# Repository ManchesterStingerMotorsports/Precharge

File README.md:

# Precharge
Circuit used to prepare the vehicle side of the TS for the full accumulator voltage.

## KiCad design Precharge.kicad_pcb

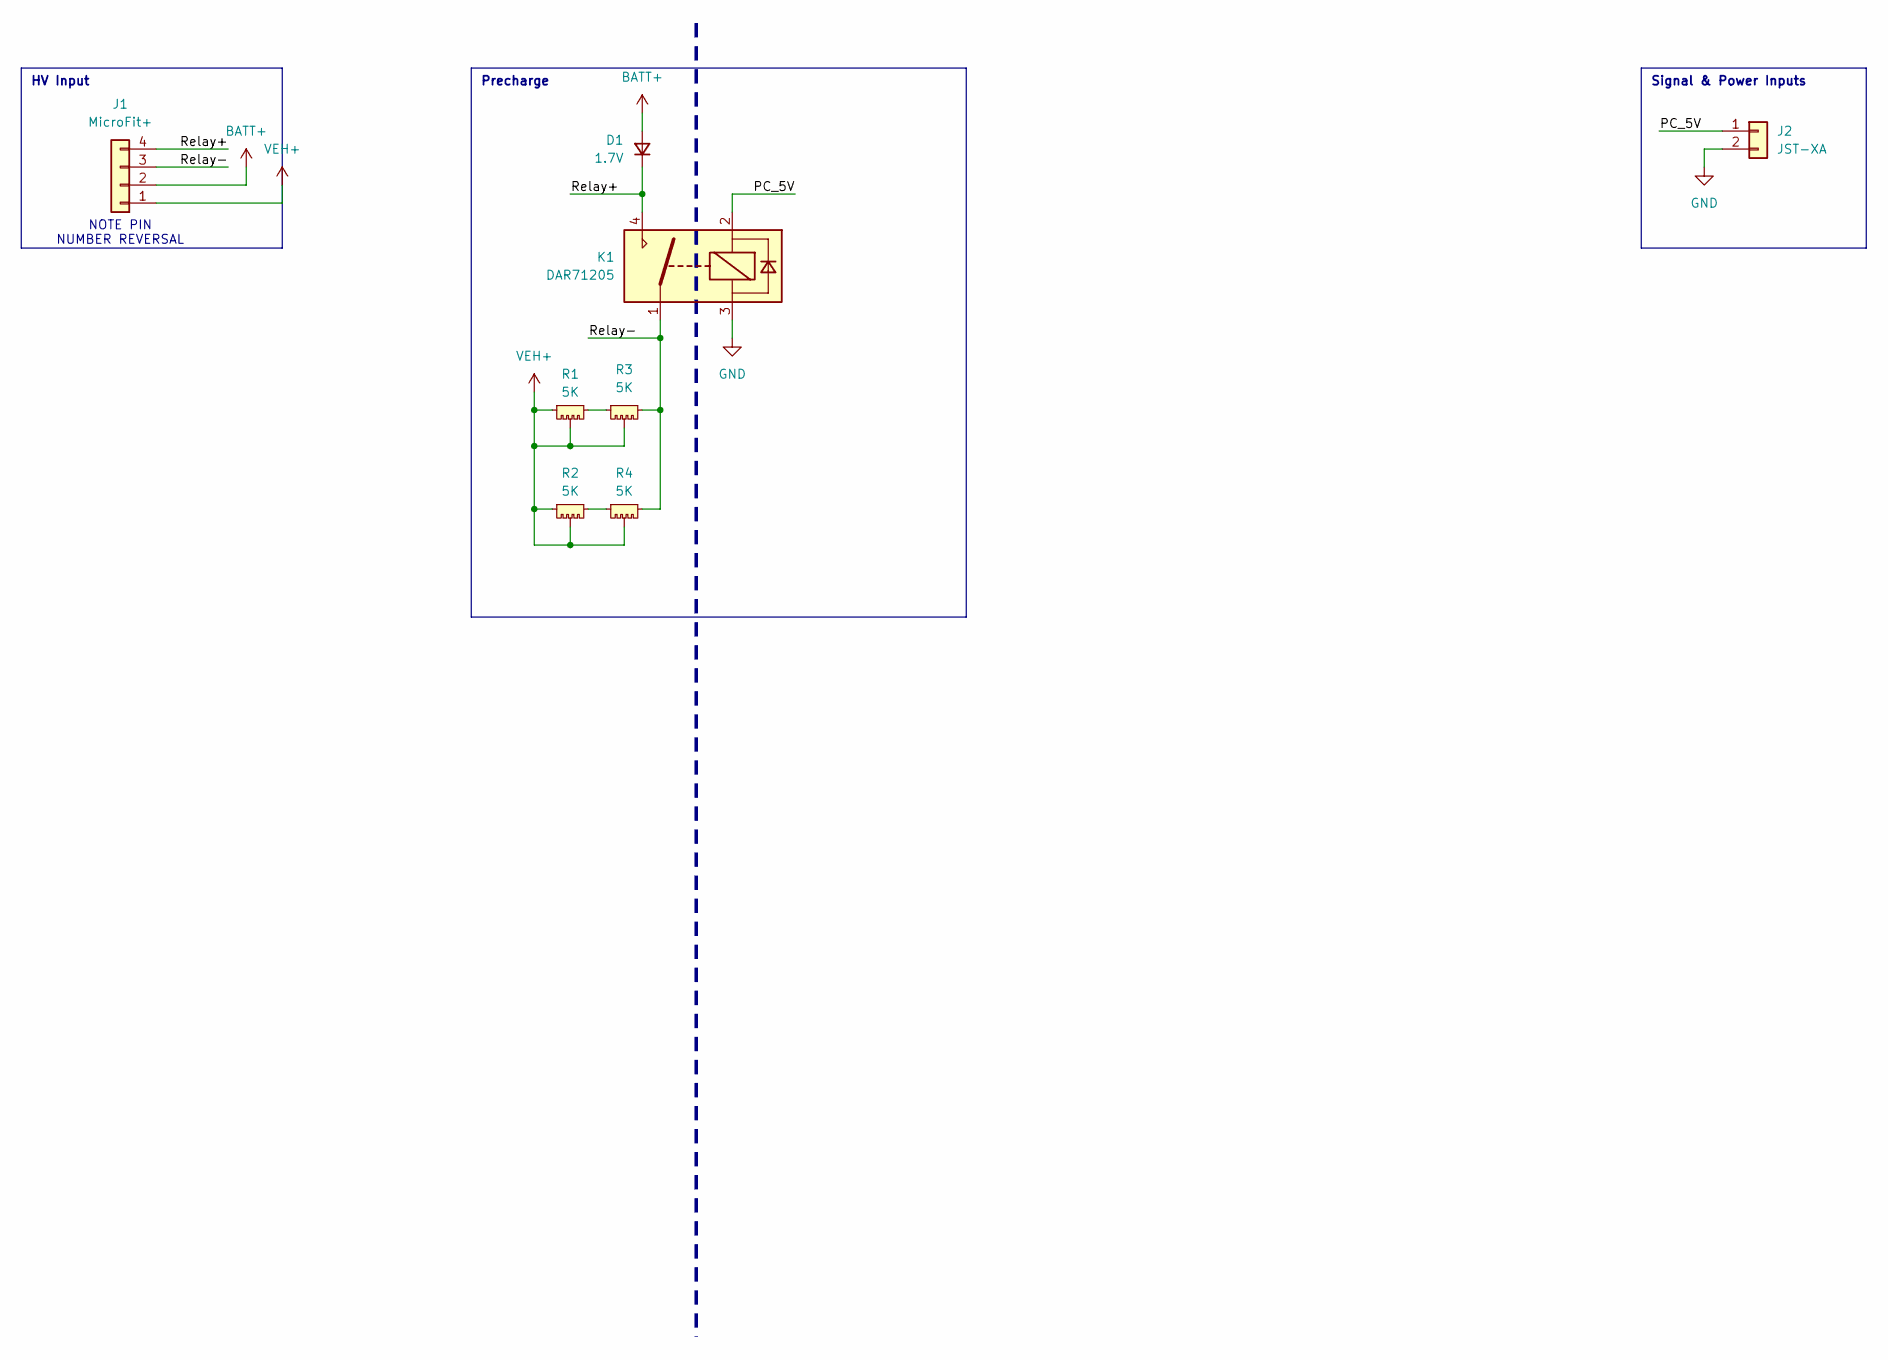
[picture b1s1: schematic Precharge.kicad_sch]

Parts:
D1: 1.7V; D_SOD-123F
J1: MicroFit+; Connector_MicroFit-Plus_4POS
J2: JST-XA; Connector_JST-XA_2POS
K1: DAR71205; Relay_HV
R1, R2, R3, R4: 5K; TO-263-2

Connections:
/PC_5V: J2.1, K1.2
/Relay+: D1.1 (K), J1.4, K1.4
/Relay-: J1.3, K1.1, R3.3, R4.3
BATT+: D1.2 (A), J1.2
GND: J2.2, K1.3
unnamed: R1.3, R3.1
unnamed: R2.3, R4.1
VEH+: J1.1, R1.1, R1.2, R2.1, R2.2, R3.2, R4.2

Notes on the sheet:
NOTE PIN NUMBER REVERSAL
Precharge
HV Input
Signal & Power Inputs

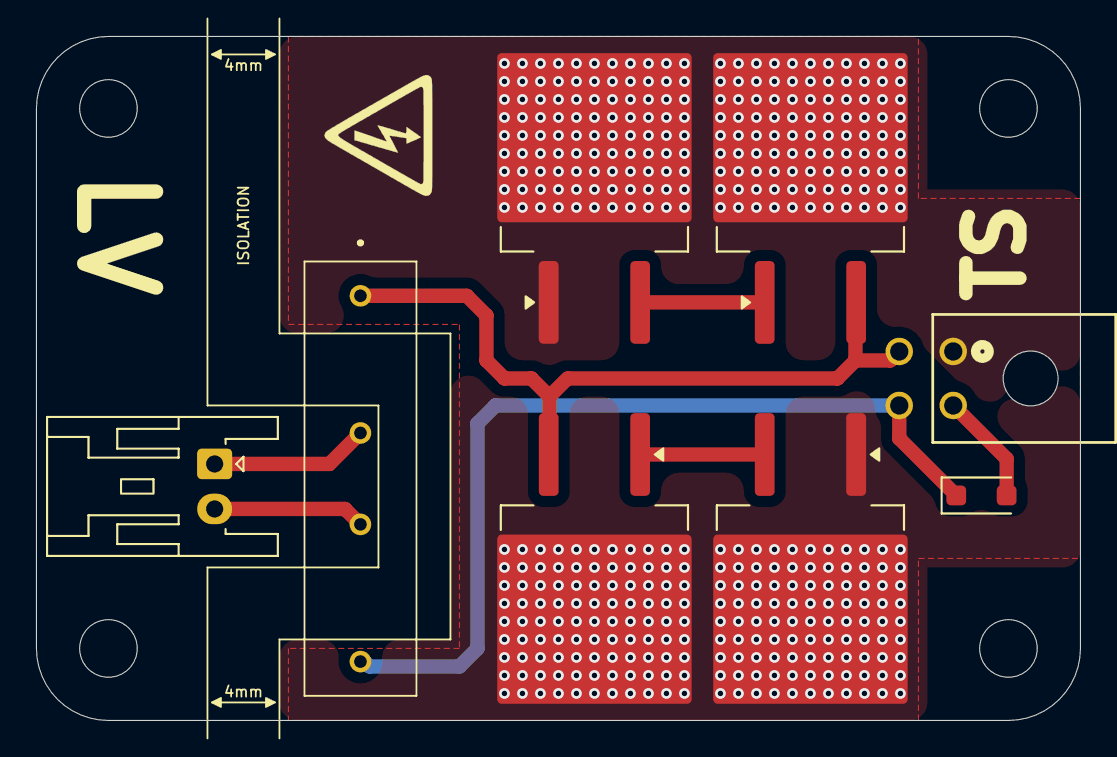
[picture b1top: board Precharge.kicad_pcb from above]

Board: 2 copper layers, 58.0 x 38.0 mm, 8 parts (0 on the bottom side), 8 nets.

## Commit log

2025-09-08 Initial Upload
2026-04-21 New schematic
2026-04-22 Finished schematic and PCB
2026-04-22 Downsized to extra small
    New relay, longer precharge time, option to shorten and add parallel resistors for lower load
2026-04-23 TSAL compatibility, shortened precharge, simpler LV
    Back to 4 resistors, so short precharge time, and powering relay from BMS GPIO. Cut SCS and regulation. added TSAL circuitry to allow for relay state measurement with single contact.
